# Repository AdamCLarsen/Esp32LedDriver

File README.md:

# Esp32 LED Driver

An ESP32 LED Driver for use with [ESPHome](https://esphome.io/index.html).  Supports 12 volt and 24 volt LEDs.

### NOTE:

This was a fun project I did for myself, where I added a few minor things I wanted, and maybe you will learn something from what I put together. However after I finished by baord, I found QuinLED, I recommend you go look at [QuinLED-An-Deca](https://quinled.info/quinled-an-deca/) over having my board manufactured.

## Goals

* Work with 24 Volt LEDs, at least 1.5 amps
* Independed control of two RGB-W strips, or eight white LED Strips
* Work well with Home Assistant
* Built in power monitoring
* Price is $50 to $75 per board

## Pin assignment on ESP32

* Test LED - ~IO19 (was ~IO13 in V1)
* SDA - IO21
* SCL - IO22
* INA219 - i2c address - 45
* CHAN 1 - IO32
* CHAN 2 - IO33
* CHAN 3 - IO25
* CHAN 4 - IO26
* CHAN 5 - IO27
* CHAN 6 - IO18
* CHAN 7 - IO17
* CHAN 8 - IO16

## The result

## Case

I have designed a case for it as well over on [OnShape](https://cad.onshape.com/documents/408e2383d926b3595b2bb312/w/fd92e074be70698e5e0da078/e/0ab2fa066dd2b40c54c9b8b1?renderMode=0&uiState=61bd8b5acb34920ff4b042c0) for use with a 3D printer.

Print uses M3 3D Printing Brass Nuts, 5mm x 6mm Embedment.  Found them on [Amazon here](https://www.amazon.com/gp/product/B09KZSJS88/).

## Other resources

* [WLED](https://kno.wled.ge/) Software that also runs on ESP32 and should work on this board using the Analog controls, if you don't have HA or don't use ESPHome.
* [QuinLED-An-Deca](https://quinled.info/quinled-an-deca/) Use this board over my board.

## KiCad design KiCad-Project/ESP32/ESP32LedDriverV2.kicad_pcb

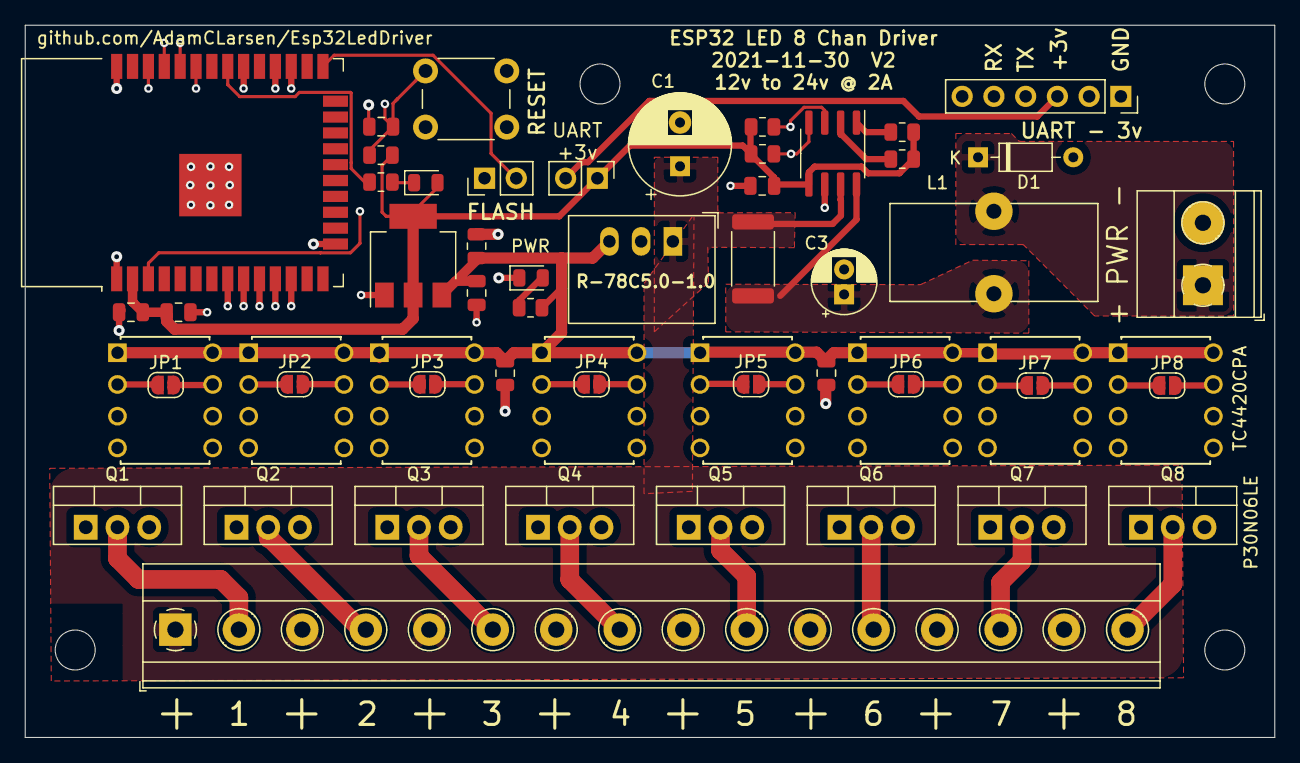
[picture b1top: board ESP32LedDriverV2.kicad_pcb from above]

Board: 4 copper layers, 100.0 x 57.0 mm, 60 parts (0 on the bottom side), 42 nets.

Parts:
C1: 330uF; CP_Radial_D8.0mm_P3.50mm
C2, C6, C9: 0.1uF; C_0805_2012Metric
C3: 100uF; CP_Radial_D5.0mm_P2.00mm
C4: 1uF; C_0805_2012Metric
C5, C7, C8: 22uF; C_0805_2012Metric
C10: 10uf; C_0805_2012Metric
D1: D_Zener 25v; D_DO-35_SOD27_P7.62mm_Horizontal
H1, H2, H3, H4: MountingHole; MountingHole_3.2mm_M3
J1: Power; TerminalBlock_Phoenix_MKDS-1,5-2_1x02_P5.00mm_Horizontal
J2: LED Terminal; TerminalBlock_Phoenix_MKDS-1,5-16-5.08_1x16_P5.08mm_Horizon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
J3: UART; PinSocket_1x06_P2.54mm_Vertical
JP1, JP2, JP3, JP4, JP5, JP6, JP7, JP8: Driver Bypass; SolderJumper-2_P1.3mm_Open_RoundedPad1.0x1.5mm
JP9: FLASH; PinHeader_1x02_P2.54mm_Vertical
JP10: UART_VCC; PinHeader_1x02_P2.54mm_Vertical
L1: 100uH; L_Toroid_Vertical_L16.4mm_W7.6mm_P6.60mm_Vishay_TJ3
LED1: PWR LED; LED_0805_2012Metric
LED2: IO13_LED; LED_0805_2012Metric
Q1, Q2, Q3, Q4, Q5, Q6, Q7, Q8: P30N06LE; TO-220-3_Vertical
R1: 0.1Ω 1% 1W; R_2512_6332Metric
R2, R3, R4, R5, R7: 10K; R_0805_2012Metric
R6: 2.2K; R_0805_2012Metric
R8: 200; R_0805_2012Metric
SW1: RESET; SW_PUSH_6mm
U1: R-78C5.0-1.0; Converter_DCDC_RECOM_R-78E-0.5_THT
U2: INA219AxD; SOIC-8_3.9x4.9mm_P1.27mm
U3, U4, U5, U6, U7, U8, U9, U10: TC4420CPA; DIP254P762X533-8
U11: AMS1117-3.3; SOT-223-3_TabPin2
U12: ESP32-WROOM-32

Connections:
+3V3: C2.1, C9.1, C10.1, JP10.1, LED2.2, R2.1, R3.1, R4.1, R5.1, R7.1, U2.5, U11.2, U12.2
+5V: C4.1, C5.1, C7.1, C8.1, R6.1, U1.3, U3.1, U3.8, U4.1, U4.8, U5.1, U5.8, U6.1, U6.8, U7.1, U7.8, U8.1, U8.8, U9.1, U9.8, U10.1, U10.8, U11.3
+24V: C1.1, J2.1, J2.3, J2.5, J2.7, J2.9, J2.11, J2.13, J2.15, R1.1, U1.1, U2.7
+24V_IN: C3.1, L1.2, R1.2, U2.8
+24V_SW: D1.1, J1.1, L1.1
/ESP32/UART_RX: J3.4, U12.34
/ESP32/UART_TX: J3.5, U12.35
/ESP32/UART_VCC: J3.3, JP10.2
/ESP32/~FLASH: JP9.2, U12.25
/ESP32/~RESET: C6.1, R7.2, SW1.2, U12.3
/Z1: JP1.1, U3.2, U12.8
/Z1-: J2.2, Q1.2
/Z2: JP2.1, U4.2, U12.9
/Z2-: J2.4, Q2.2
/Z3: JP3.1, U5.2, U12.10
/Z3-: J2.6, Q3.2
/Z4: JP4.1, U6.2, U12.11
/Z4-: J2.8, Q4.2
/Z5: JP5.1, U7.2, U12.12
/Z5-: J2.10, Q5.2
/Z6: JP6.1, U8.2, U12.30
/Z6-: J2.12, Q6.2
/Z7: JP7.1, U9.2, U12.28
/Z7-: J2.14, Q7.2
/Z8: JP8.1, U10.2, U12.27
/Z8-: J2.16, Q8.2
GND: C1.2, C2.2, C3.2, C4.2, C5.2, C6.2, C7.2, C8.2, C9.2, C10.2, D1.2, J1.2, J3.1, JP9.1, LED1.1, Q1.3, Q2.3, Q3.3, Q4.3, Q5.3, Q6.3, Q7.3, Q8.3, SW1.1, U1.2, U2.6, U3.4, U3.5, U4.4, U4.5, U5.4, U5.5, U6.4, U6.5, U7.4, U7.5, U8.4, U8.5, U9.4, U9.5, U10.4, U10.5, U11.1, U12.1, U12.15, U12.38, U12.39
unnamed: JP1.2, Q1.1, U3.7
unnamed: JP2.2, Q2.1, U4.7
unnamed: JP3.2, Q3.1, U5.7
unnamed: JP4.2, Q4.1, U6.7
unnamed: JP5.2, Q5.1, U7.7
unnamed: JP6.2, Q6.1, U8.7
unnamed: JP7.2, Q7.1, U9.7
unnamed: JP8.2, Q8.1, U10.7
unnamed: LED1.2, R6.2
unnamed: LED2.1, R8.2
unnamed: R4.2, U2.1
unnamed: R5.2, U2.2
unnamed: R8.1, U12.31
SCL: R3.2, U2.4, U12.36
SDA: R2.2, U2.3, U12.33

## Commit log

2021-11-13 Init Check-in
2021-11-13 swap out 603 resistors for 805
    Give us more room to work with if we have to fix something.
2021-11-13 Switch power direction detection to SMD
2021-11-14 Fixes in prep for printing
    Making sure tolerance are in-spec for JLC PCB
2021-11-14 Fix Power Mosfet direction
2021-11-14 Fix pin header
2021-11-15 Enable to bottom mask layer
2021-11-15 Refine PCB layout
    Added GPIO labels to the bottom of the board
    updates to ESP32 power and ground traces
    Removed zip file of plot files.
2021-11-16 Increased trace width for +24v net
2021-12-01 Removed reverse voltage and increased size of power traces
    Reverse voltage needed different components for 24 volt, and was a nice to have, so to keep cost down, opted to remove it.
2021-12-01 Jumper to connect UART VCC to 5v
    Allow powering the 3v-5v side from the UART conector.
2021-12-02 Update fill zones
2021-12-04 Move on board test LED to a better pin. and swap TX/RX UART pins
2021-12-04 Aligning parts to each other
2021-12-04 More clean up of PCB layout
2021-12-16 update pin labels
2021-12-16 Reset annotations
2021-12-18 Added ESPHome Yaml
